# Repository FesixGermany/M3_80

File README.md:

All files about the school project M3.80 we developed in a group of four in 2015.

See documentation/description_en.pdf or Beschreibung_DE.pdf for more info.

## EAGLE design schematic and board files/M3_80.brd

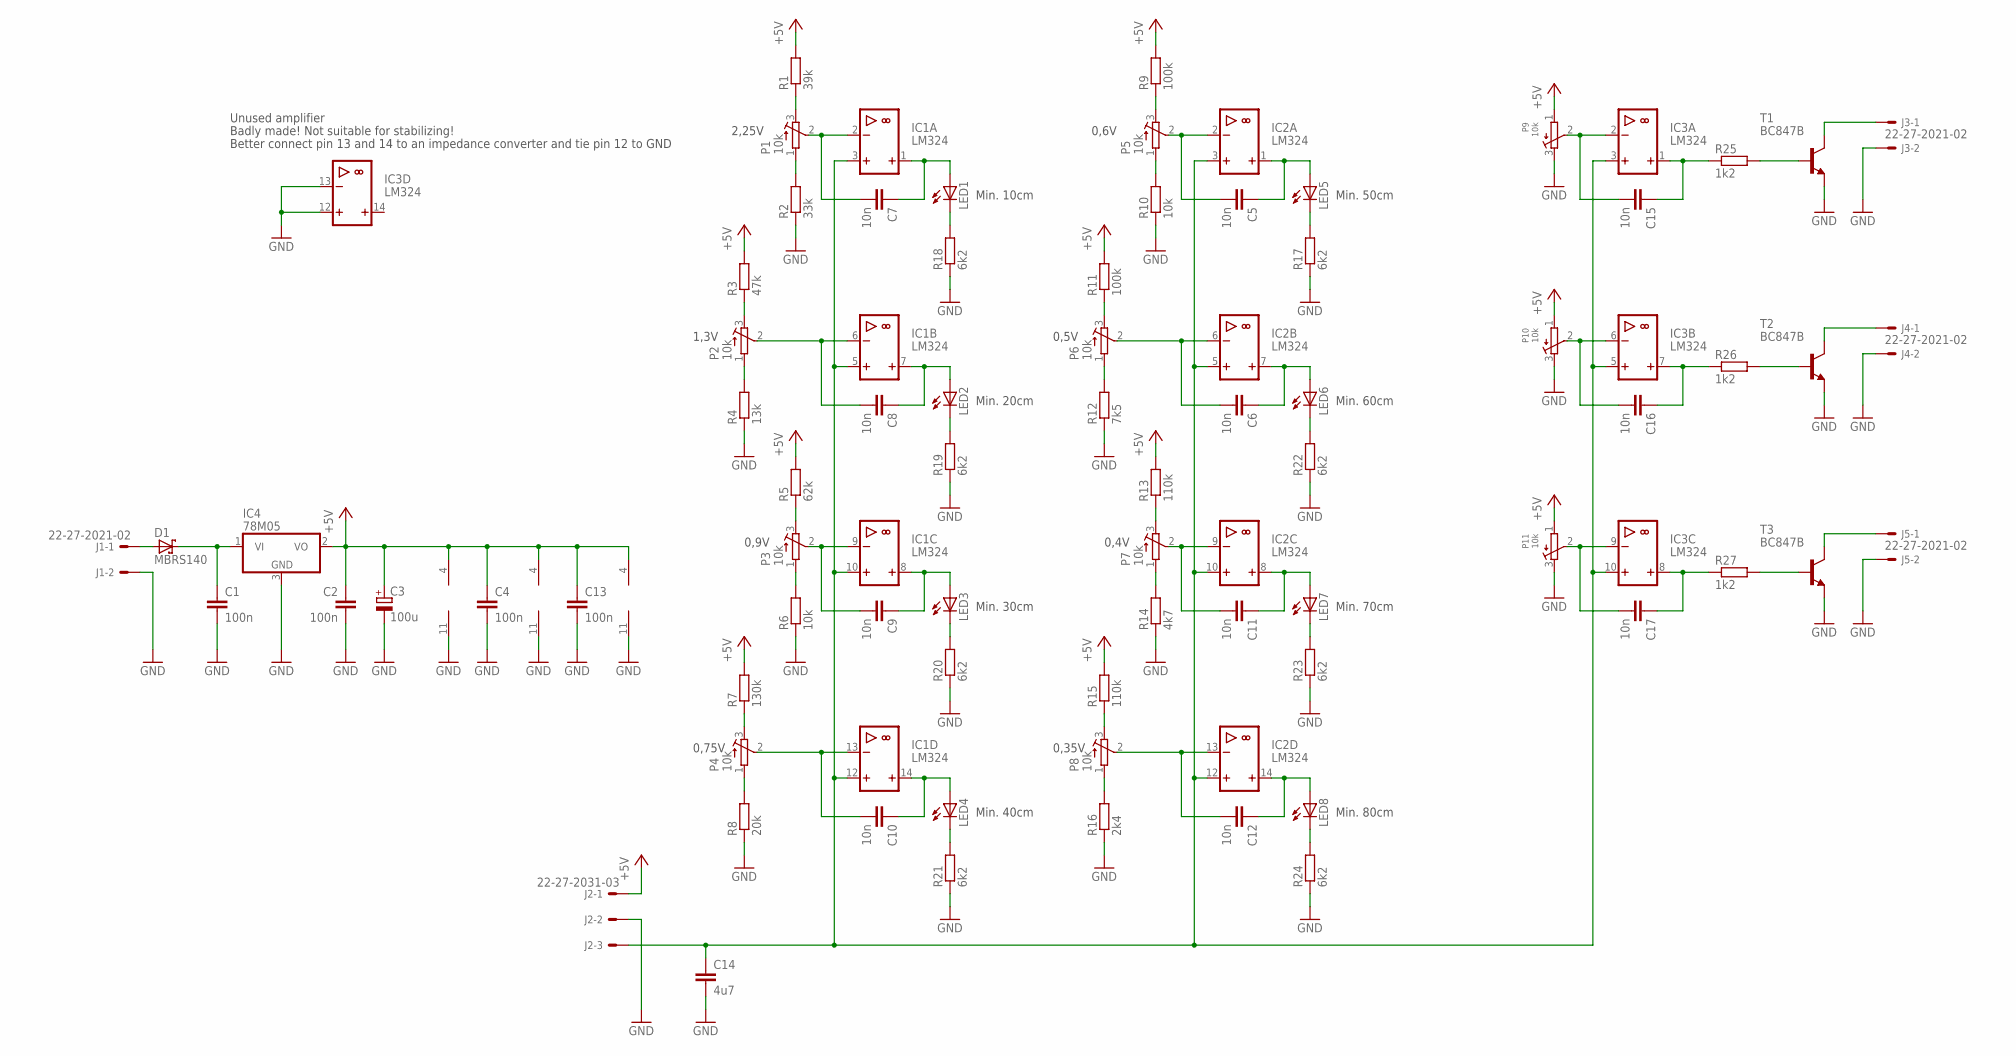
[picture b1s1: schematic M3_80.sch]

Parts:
C1, C2, C4, C13: 100n; C0805K
C3: 100u; D/7343-31W
C5, C6, C7, C8, C9, C10, C11, C12, C15, C16, C17: 10n; C0805K
C14: 4u7; C0805K
D1: MBRS140; SMB
IC1, IC2, IC3: LM324; SO14
IC4: 78M05; TO252
J1, J3, J4, J5: 22-27-2021-02; 6410-02
J2: 22-27-2031-03; 6410-03
LED1, LED2, LED3, LED4, LED5, LED6, LED7, LED8: LED3MM
P1, P2, P3, P4, P5, P6, P7, P8: 10k; EVM1D
P9, P10, P11: 10k; T63YA
R1: 39k; M0805
R2: 33k; M0805
R3: 47k; M0805
R4: 13k; M0805
R5: 62k; M0805
R6, R10: 10k; M0805
R7: 130k; M0805
R8: 20k; M0805
R9, R11: 100k; M0805
R12: 7k5; M0805
R13, R15: 110k; M0805
R14: 4k7; M0805
R16: 2k4; M0805
R17, R18, R19, R20, R21, R22, R23, R24: 6k2; M0805
R25, R26, R27: 1k2; M0805
T1, T2, T3: BC847B; SOT23

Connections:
+5V: C2.1, C3.+, C4.1, C13.1, IC1.4 (V+), IC2.4 (V+), IC3.4 (V+), IC4.2 (VO), J2.1, P9.1, P10.1, P11.1, R1.2, R3.2, R5.2, R7.2, R9.2, R11.2, R13.2, R15.2
GND: C1.2, C2.2, C3.-, C4.2, C13.2, C14.2, IC1.11 (V-), IC2.11 (V-), IC3.11 (V-), IC3.12 (+IN), IC3.13 (-IN), IC4.3 (GND), J1.2, J2.2, J3.2, J4.2, J5.2, P9.3, P10.3, P11.3, R2.1, R4.1, R6.1, R8.1, R10.1, R12.1, R14.1, R16.1, R17.1, R18.1, R19.1, R20.1, R21.1, R22.1, R23.1, R24.1, T1.2 (E), T2.2 (E), T3.2 (E)
unnamed: C1.1, D1.C, IC4.1 (VI)
unnamed: C7.2, IC1.2 (-IN), P1.2
unnamed: C8.2, IC1.6 (-IN), P2.2
unnamed: C9.2, IC1.9 (-IN), P3.2
unnamed: C10.2, IC1.13 (-IN), P4.2
unnamed: C5.2, IC2.2 (-IN), P5.2
unnamed: C6.2, IC2.6 (-IN), P6.2
unnamed: C11.2, IC2.9 (-IN), P7.2
unnamed: C12.2, IC2.13 (-IN), P8.2
unnamed: C5.1, IC2.1 (OUT), LED5.A
unnamed: LED5.K (C), R17.2
unnamed: C8.1, IC1.7 (OUT), LED2.A
unnamed: LED2.K (C), R19.2
unnamed: C7.1, IC1.1 (OUT), LED1.A
unnamed: LED1.K (C), R18.2
unnamed: C9.1, IC1.8 (OUT), LED3.A
unnamed: LED3.K (C), R20.2
unnamed: C10.1, IC1.14 (OUT), LED4.A
unnamed: LED4.K (C), R21.2
unnamed: C6.1, IC2.7 (OUT), LED6.A
unnamed: LED6.K (C), R22.2
unnamed: C11.1, IC2.8 (OUT), LED7.A
unnamed: LED7.K (C), R23.2
unnamed: C12.1, IC2.14 (OUT), LED8.A
unnamed: LED8.K (C), R24.2
unnamed: P5.3, R9.1
unnamed: P5.1, R10.2
unnamed: P6.3, R11.1
unnamed: P6.1, R12.2
unnamed: P7.3, R13.1
unnamed: P7.1, R14.2
unnamed: P8.3, R15.1
unnamed: P1.3, R1.1
unnamed: P8.1, R16.2
unnamed: C16.2, IC3.6 (-IN), P10.2
unnamed: C15.2, IC3.2 (-IN), P9.2
unnamed: C17.2, IC3.9 (-IN), P11.2
unnamed: P1.1, R2.2
unnamed: D1.A, J1.1
unnamed: P2.3, R3.1
unnamed: P2.1, R4.2
unnamed: P3.3, R5.1
unnamed: P3.1, R6.2
unnamed: P4.3, R7.1
unnamed: P4.1, R8.2
unnamed: C15.1, IC3.1 (OUT), R25.1
unnamed: R25.2, T1.1 (B)
unnamed: C16.1, IC3.7 (OUT), R26.1
unnamed: R26.2, T2.1 (B)
unnamed: C17.1, IC3.8 (OUT), R27.1
unnamed: R27.2, T3.1 (B)
unnamed: J5.1, T3.3 (C)
unnamed: J4.1, T2.3 (C)
unnamed: J3.1, T1.3 (C)
unnamed: C14.1, IC1.3 (+IN), IC1.5 (+IN), IC1.10 (+IN), IC1.12 (+IN), IC2.3 (+IN), IC2.5 (+IN), IC2.10 (+IN), IC2.12 (+IN), IC3.3 (+IN), IC3.5 (+IN), IC3.10 (+IN), J2.3

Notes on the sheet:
Min. 10cm
Min. 20cm
Min. 30cm
Min. 40cm
2,25V
1,3V
0,9V
0,75V
Min. 50cm
Min. 60cm
Min. 70cm
Min. 80cm
0,6V
0,5V
0,4V
0,35V
Unused amplifier
Badly made! Not suitable for stabilizing!
Better connect pin 13 and 14 to an impedance converter and tie pin 12 to GND

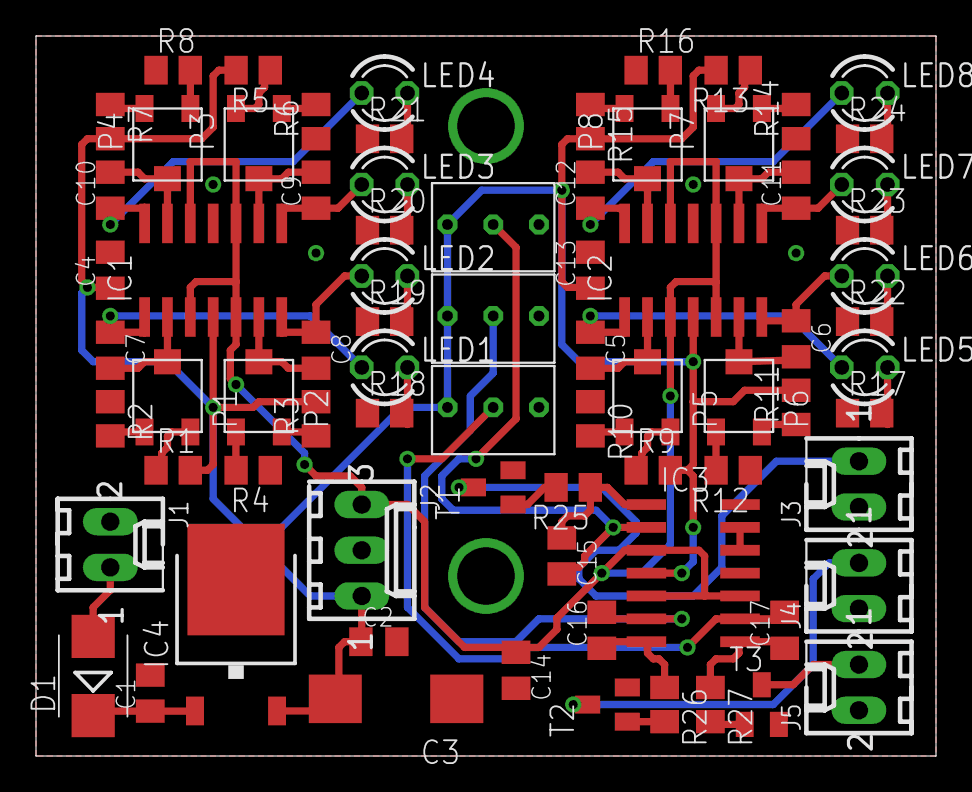
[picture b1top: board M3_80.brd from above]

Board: 2 copper layers, 50.0 x 40.0 mm, 76 parts (0 on the bottom side), 57 nets.
